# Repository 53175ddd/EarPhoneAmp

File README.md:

# EarPhoneAmp

秋月で買える部品で作るイヤホンアンプキット

# 部品表

| アノテーション | 部品名 | 秋月リンク |
|:----|:----|:----|
| C1 ~ C4 | 0.1uF      | <https://akizukidenshi.com/catalog/g/gP-10147/> |
| C5, C6  | 47uF       | <https://akizukidenshi.com/catalog/g/gP-04627/> |
| C7, C8  | 100uF      | <https://akizukidenshi.com/catalog/g/gP-04628/> |
| J1, J2  | 3.5mm Jack | <https://akizukidenshi.com/catalog/g/gC-02460/> |
| J3      | DC Jack    | <https://akizukidenshi.com/catalog/g/gC-06568/> |
| R1 ~ R6 | 10kΩ       | <https://akizukidenshi.com/catalog/g/gR-25103/> |
| R7, R8  | 1MΩ        | <https://akizukidenshi.com/catalog/g/gR-25105/> |
| RV1     | 10kΩ A     | <https://akizukidenshi.com/catalog/g/gP-03604/> |
| U1, U2  | OPAmp      | <https://akizukidenshi.com/catalog/g/gP-00017/> |
| U3      | NJM7805    | <https://akizukidenshi.com/catalog/g/gI-08678/> |

可変抵抗に [つまみ](https://akizukidenshi.com/catalog/g/gP-12202/) を取り付けて使用してください

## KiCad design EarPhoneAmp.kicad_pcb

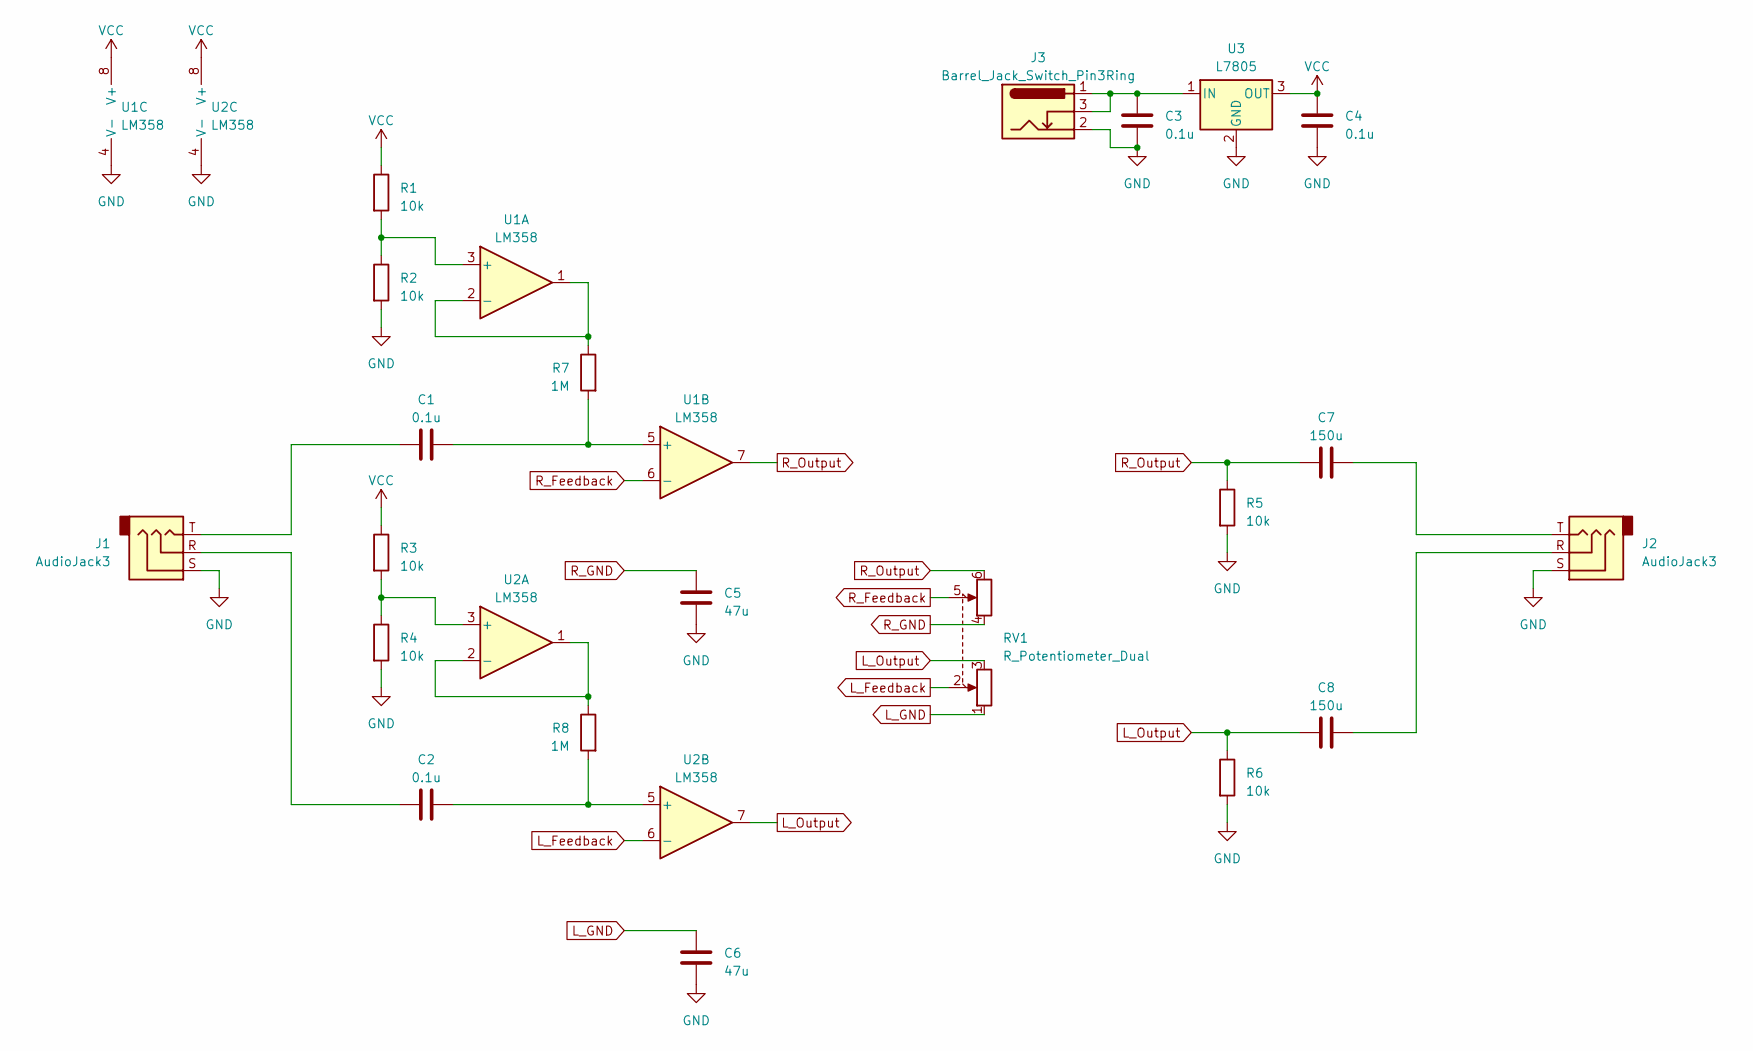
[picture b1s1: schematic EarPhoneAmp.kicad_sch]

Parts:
C1, C2, C3, C4: 0.1u; C_Disc_D5.0mm_W2.5mm_P5.00mm
C5, C6: 47u; CP_Radial_D6.3mm_P2.50mm
C7, C8: 150u; CP_Radial_D10.0mm_P5.00mm
J1: AudioJack3; Jack_3.5mm_Switronic_ST-005-G_horizontal
J2: AudioJack3; Jack_3.5mm_Lumberg_1503_07_Horizontal
J3: Barrel_Jack_Switch_Pin3Ring; BarrelJack_Horizontal
R1, R2, R3, R4, R5, R6: 10k; R_Axial_DIN0204_L3.6mm_D1.6mm_P7.62mm_Horizontal
R7, R8: 1M; R_Axial_DIN0204_L3.6mm_D1.6mm_P7.62mm_Horizontal
RV1: R_Potentiometer_Dual; Potentiometer_Alps_RK097_Dual_Horizontal
U1, U2: LM358; DIP-8_W7.62mm_Socket
U3: L7805; TO-220-3_Vertical

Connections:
GND: C3.2, C4.2, C5.2, C6.2, J1.S, J2.S, J3.2, R2.2, R4.2, R5.2, R6.2, U1.4 (V-), U2.4 (V-), U3.2 (GND)
L_Feedback: RV1.2, U2.6 (-)
L_GND: C6.1, RV1.1
L_Output: C8.1, R6.1, RV1.3, U2.7
unnamed: C1.1, J1.T
unnamed: C2.1, J1.R
unnamed: C7.2, J2.T
unnamed: C8.2, J2.R
unnamed: R1.2, R2.1, U1.3 (+)
unnamed: R7.1, U1.1, U1.2 (-)
unnamed: C1.2, R7.2, U1.5 (+)
unnamed: R3.2, R4.1, U2.3 (+)
unnamed: R8.1, U2.1, U2.2 (-)
unnamed: C2.2, R8.2, U2.5 (+)
unnamed: C3.1, J3.1, J3.3, U3.1 (IN)
R_Feedback: RV1.5, U1.6 (-)
R_GND: C5.1, RV1.4
R_Output: C7.1, R5.1, RV1.6, U1.7
VCC: C4.1, R1.1, R3.1, U1.8 (V+), U2.8 (V+), U3.3 (OUT)

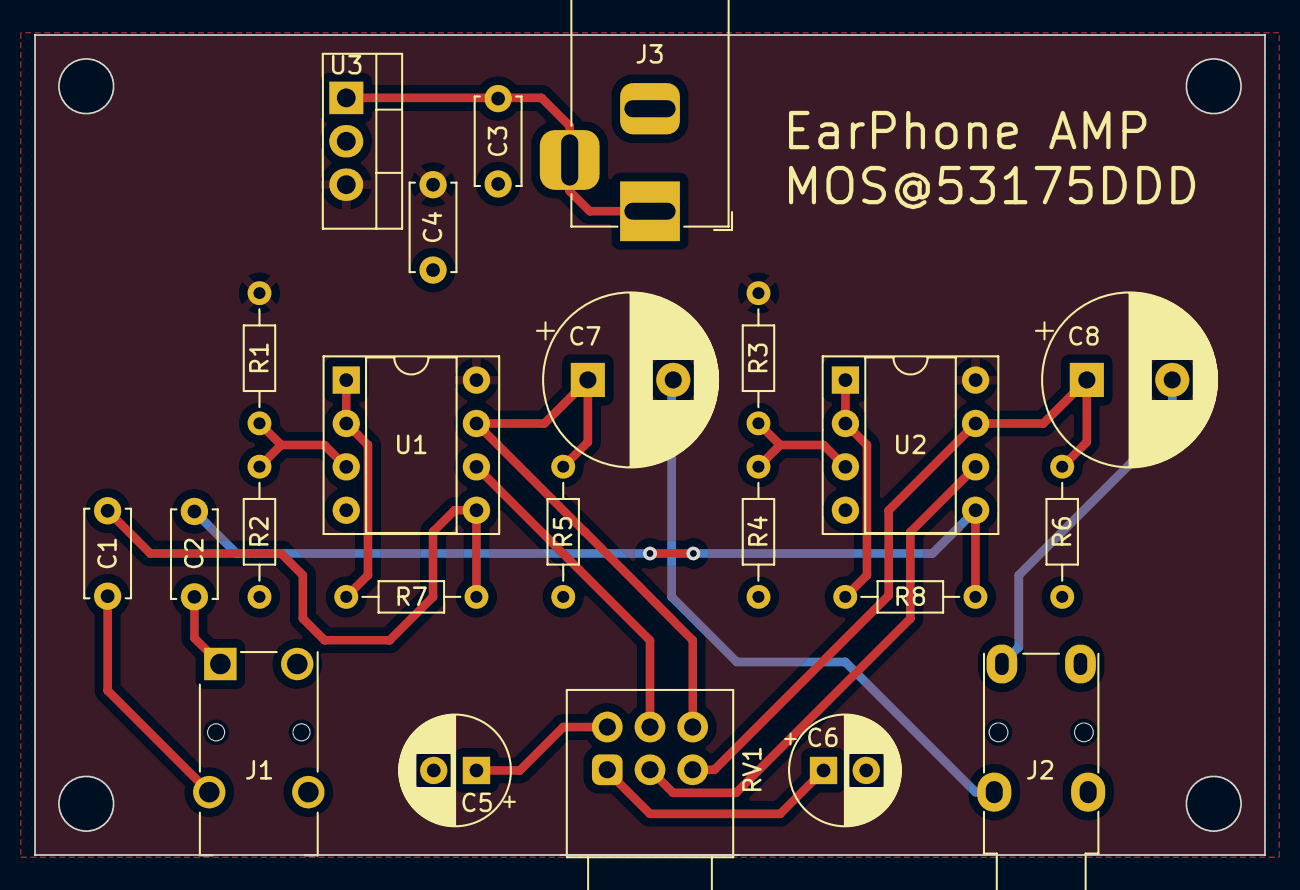
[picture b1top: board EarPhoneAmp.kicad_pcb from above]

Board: 2 copper layers, 72.0 x 48.0 mm, 23 parts (0 on the bottom side), 19 nets.

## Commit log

2023-12-27 部品表作成
